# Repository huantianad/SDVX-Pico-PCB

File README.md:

# SDVX Pico PCB

A quick and dirty custom PCB I designed for use with a Raspberry Pi Pico. Wired up for 7 buttons and 2 knobs, and option WS2812B strip. Connectors are JST-XH, with button LEDs running off of 5V. Because of that, I used 2N2222 BJTs to toggle the LEDs off of the 3.3V on the pico.

Indended for use with a slightly tweaked [Pico-Game-Controller](https://github.com/huantianad/Pico-Game-Controller). You may have to edit the encoder PPR and encoder inversion settings.

Encoders are wired for Data, Data, +5V, GND; buttons are wired for Switch GPIO, LED GND, LED 5V, Switch GND.

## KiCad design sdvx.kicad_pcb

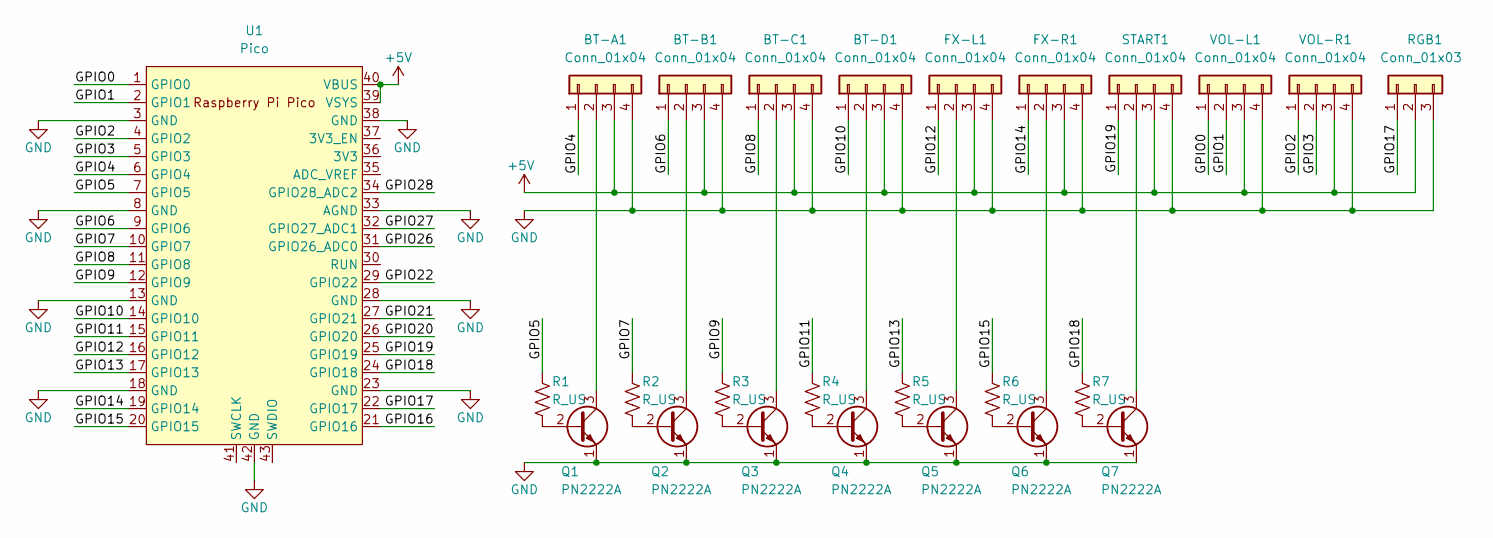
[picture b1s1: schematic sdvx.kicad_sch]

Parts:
BT-A1: Conn_01x04; JST_XH_B4B-XH-A_1x04_P2.50mm_Vertical
BT-B1: Conn_01x04; JST_XH_B4B-XH-A_1x04_P2.50mm_Vertical
BT-C1: Conn_01x04; JST_XH_B4B-XH-A_1x04_P2.50mm_Vertical
BT-D1: Conn_01x04; JST_XH_B4B-XH-A_1x04_P2.50mm_Vertical
FX-L1: Conn_01x04; JST_XH_B4B-XH-A_1x04_P2.50mm_Vertical
FX-R1: Conn_01x04; JST_XH_B4B-XH-A_1x04_P2.50mm_Vertical
Q1, Q2, Q3, Q4, Q5, Q6, Q7: PN2222A; TO-92_Inline
R1, R2, R3, R4, R5, R6, R7: R_US; R_Axial_DIN0207_L6.3mm_D2.5mm_P10.16mm_Horizontal
RGB1: Conn_01x03; JST_XH_B3B-XH-A_1x03_P2.50mm_Vertical
START1: Conn_01x04; JST_XH_B4B-XH-A_1x04_P2.50mm_Vertical
U1: Pico; RPi_Pico_SMD_TH
VOL-L1: Conn_01x04; JST_XH_B4B-XH-A_1x04_P2.50mm_Vertical
VOL-R1: Conn_01x04; JST_XH_B4B-XH-A_1x04_P2.50mm_Vertical

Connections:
+5V: BT-A1.3, BT-B1.3, BT-C1.3, BT-D1.3, FX-L1.3, FX-R1.3, RGB1.2, START1.3, U1.39 (VSYS), U1.40 (VBUS), VOL-L1.3, VOL-R1.3
/GPIO0: U1.1 (GPIO0), VOL-L1.1
/GPIO1: U1.2 (GPIO1), VOL-L1.2
/GPIO2: U1.4 (GPIO2), VOL-R1.1
/GPIO3: U1.5 (GPIO3), VOL-R1.2
/GPIO4: BT-A1.1, U1.6 (GPIO4)
/GPIO5: R1.1, U1.7 (GPIO5)
/GPIO6: BT-B1.1, U1.9 (GPIO6)
/GPIO7: R2.1, U1.10 (GPIO7)
/GPIO8: BT-C1.1, U1.11 (GPIO8)
/GPIO9: R3.1, U1.12 (GPIO9)
/GPIO10: BT-D1.1, U1.14 (GPIO10)
/GPIO11: R4.1, U1.15 (GPIO11)
/GPIO12: FX-L1.1, U1.16 (GPIO12)
/GPIO13: R5.1, U1.17 (GPIO13)
/GPIO14: FX-R1.1, U1.19 (GPIO14)
/GPIO15: R6.1, U1.20 (GPIO15)
/GPIO16: U1.21 (GPIO16)
/GPIO17: RGB1.1, U1.22 (GPIO17)
/GPIO18: R7.1, U1.24 (GPIO18)
/GPIO19: START1.1, U1.25 (GPIO19)
/GPIO20: U1.26 (GPIO20)
/GPIO21: U1.27 (GPIO21)
/GPIO22: U1.29 (GPIO22)
/GPIO26: U1.31 (GPIO26_ADC0)
/GPIO27: U1.32 (GPIO27_ADC1)
/GPIO28: U1.34 (GPIO28_ADC2)
GND: BT-A1.4, BT-B1.4, BT-C1.4, BT-D1.4, FX-L1.4, FX-R1.4, Q1.1 (E), Q2.1 (E), Q3.1 (E), Q4.1 (E), Q5.1 (E), Q6.1 (E), Q7.1 (E), RGB1.3, START1.4, U1.3 (GND), U1.8 (GND), U1.13 (GND), U1.18 (GND), U1.23 (GND), U1.28 (GND), U1.33 (AGND), U1.38 (GND), U1.42 (GND), VOL-L1.4, VOL-R1.4
unnamed: BT-A1.2, Q1.3 (C)
unnamed: BT-B1.2, Q2.3 (C)
unnamed: BT-C1.2, Q3.3 (C)
unnamed: BT-D1.2, Q4.3 (C)
unnamed: FX-L1.2, Q5.3 (C)
unnamed: FX-R1.2, Q6.3 (C)
unnamed: Q1.2 (B), R1.2
unnamed: Q2.2 (B), R2.2
unnamed: Q3.2 (B), R3.2
unnamed: Q4.2 (B), R4.2
unnamed: Q5.2 (B), R5.2
unnamed: Q6.2 (B), R6.2
unnamed: Q7.2 (B), R7.2
unnamed: Q7.3 (C), START1.2

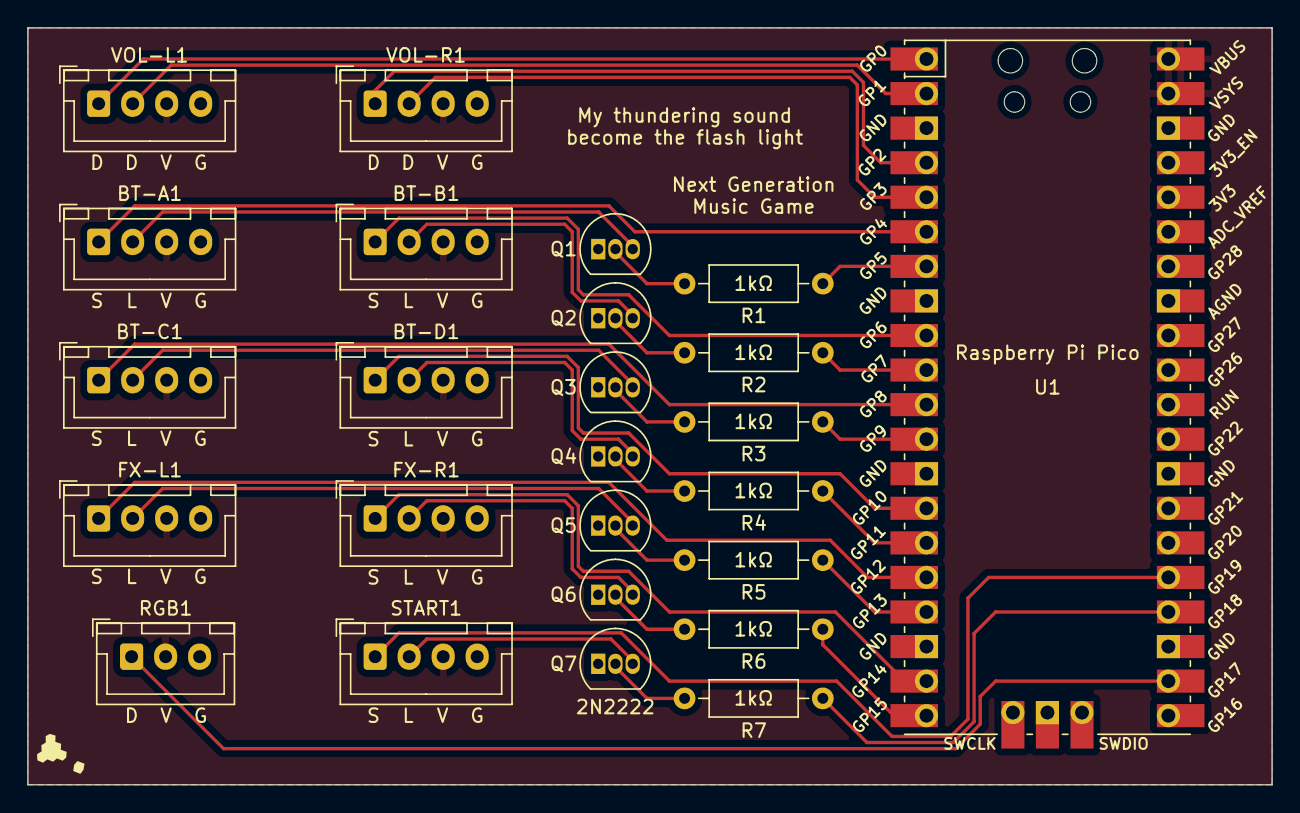
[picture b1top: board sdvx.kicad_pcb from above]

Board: 2 copper layers, 91.4 x 55.6 mm, 26 parts (0 on the bottom side), 35 nets.

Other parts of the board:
LOGO: LOGO

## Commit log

2024-02-12 README.md: specify pinout
